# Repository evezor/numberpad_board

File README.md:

# Numberpad Board
*please note this board has been deprecated.

An edge board containing with a numberpad face with 12 buttons. 

source files can be found here: hhttps://github.com/evezor/v0_numberpad_board

This board uses the Evezor Stamp STMF405 MCU

source: https://github.com/evezor/Evezor-Stamp-STMF405

Evezor® and all associated marks, logos, and designs are registered trademarks and protected by copyright. Unauthorized use or reproduction of these trademarks and copyrighted materials is strictly prohibited.

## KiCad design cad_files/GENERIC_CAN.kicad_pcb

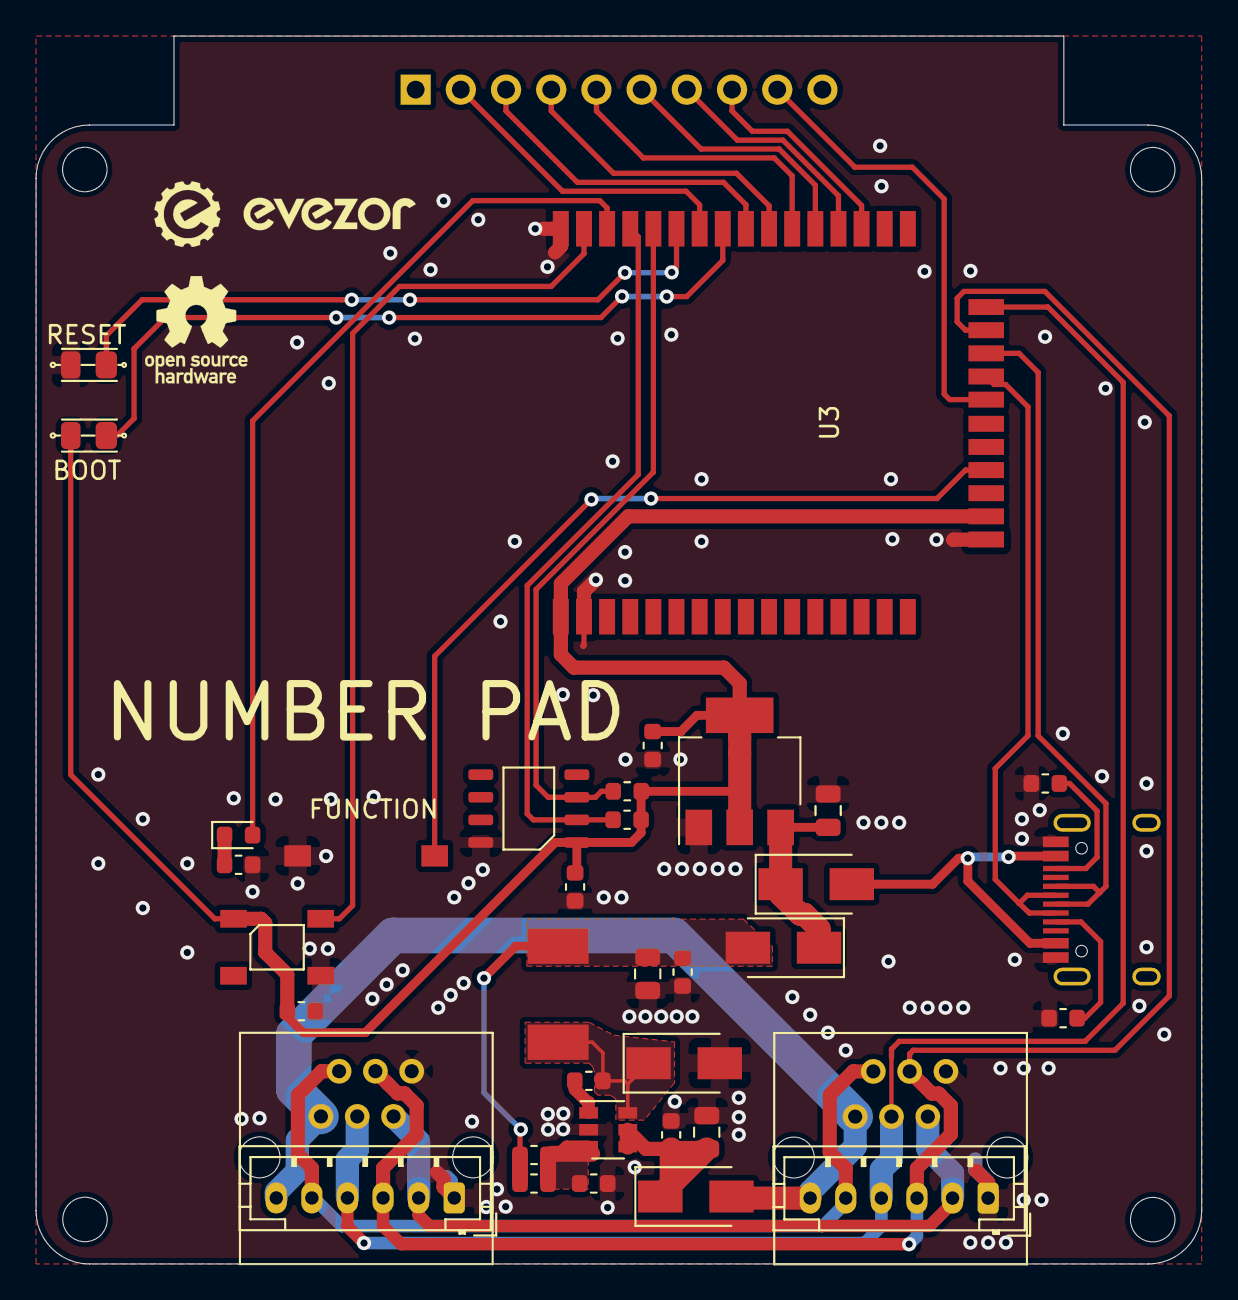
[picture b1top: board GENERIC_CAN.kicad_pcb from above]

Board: 2 copper layers, 65.5 x 69.0 mm, 41 parts (1 on the bottom side), 34 nets.

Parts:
C1, C2, C3, C5, C7, C10: .1uF; C_0603_1608Metric
C4: 4.7uF; C_0805_2012Metric
C6: 22uF; C_0805_2012Metric
C8: 10uF; C_0805_2012Metric
C9: C_Small; C_0603_1608Metric
D1, D2, D4, D5: D_Schottky; D_SMA
D3: LED; LED_0603_1608Metric
H1, H2, H3, H4: MountingHole; MountingHole_2.5mm
J1: USB_C_Receptacle_USB2.0; USB_C_Receptacle_HRO_TYPE-C-31-M-12
J2, J3: RJ11; RJ11_C189747_Horizontal
J4, J5: PH; JST_PH_B6B-PH-K_1x06_P2.00mm_Vertical
J6: Conn_01x10; PinSocket_1x10_P2.54mm_Vertical
JP1: RESET; SHORT_PAD
JP2: BOOT; SHORT_PAD
L1: 22uH; INDUCTOR_7.5X6.6_GCDA0630-220MC
R1, R5: 15k; R_0603_1608Metric
R2: 82k; R_0603_1608Metric
R3, R4: 5.1k; R_0603_1608Metric
R6, R7: R_Small; R_0603_1608Metric
SW1: SW_Push; SWITCH_2x3_SMD_TACTILE_GREEN
U1: V_REG; SOT-23-6
U2: AMS1117-3.3; SOT-223-3_TabPin2
U3: EDGE_STM32F405_CPU_V1; EDGE_STAMP
U4: MICOCONTROLLER_GUID_SOP-8; GUID_PS150C
U6: NEOPIXEL_5050

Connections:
+3V3: C7.1, C9.1, C10.1, JP2.2, R6.2, R7.2, U2.2, U3.1, U3.18, U4.1, U6.1
+48V: D2.2, J2.6, J3.6, J4.6, J5.6
/BOOT: JP2.1, U3.36
/CAN_H: J2.3, J3.3, J4.3, J5.3, U3.26
/CAN_L: J2.4, J3.4, J4.4, J5.4, U3.27
/CC1: J1.A5, R4.1
/CC2: J1.B5, R3.1
/COL_1: J6.2, U3.37
/COL_2: J6.3, U3.35
/COL_3: J6.4, U3.34
/COL_4: J6.5, U3.33
/D+: J1.A6, J1.B6, U3.25
/D-: J1.A7, J1.B7, U3.24
/FD_H: J2.2, J3.2, J4.2, J5.2
/FD_L: J2.5, J3.5, J4.5, J5.5
/FUNCTION_BUTTON: SW1.1, U3.20
/GUID_SCL: R7.1, U3.39, U4.3
/GUID_SDO: R6.1, U3.40, U4.2
/HBT_LED: D3.2, U3.41
/NEO_STATUS: U3.42, U6.4
/RESET: JP1.1, U3.38
/ROW_1: J6.6, U3.32
/ROW_2: J6.7, U3.31
/ROW_3: J6.8, U3.30
/ROW_4: J6.9, U3.23
/USB_VCC: D4.2, J1.A4, J1.A9, J1.B4, J1.B9
/VREG_OUT: C2.1, C5.1, C6.1, D5.2, L1.2, R2.1
GND: C3.2, C4.2, C5.2, C6.2, C7.2, C8.2, C9.2, C10.2, D1.2, J1.A1, J1.A12, J1.B1, J1.B12, J2.1, J3.1, J4.1, J5.1, JP1.2, R1.1, R3.2, R4.2, R5.1, SW1.2, U1.2, U2.1, U3.2, U3.17, U3.43, U4.8, U6.3
unnamed: C1.1, D1.1, L1.1, U1.6
unnamed: C1.2, U1.1
unnamed: C2.2, R1.2, R2.2, U1.3
unnamed: C3.1, C4.1, D2.1, U1.4, U1.5
unnamed: C8.1, D4.1, D5.1, U2.3
unnamed: D3.1, R5.2

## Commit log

2023-09-11 add pics
2023-09-11 Update #auto_saved_files#
